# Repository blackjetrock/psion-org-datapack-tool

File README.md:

# psion-org-datapack-tool
Datapack tool for Psion Organisers

Status
======

** This is a work in progress and probably always will be **

The code builds and can read datapack data. It can also write datapack data. issues:
the OLED and buttons work and there are read and write and info options that work on the OLED.
A lot of funtionality is over USB serial.

0. There are errors on the fab1 PCB. these are listed in the errata. hand mods are needed to get the PCB to work.
1. Flash packs can't be written.
2. Read pak to file doesn't seem to give a valid opk file, not sure why
3. Detection of all the diffferent pack addressing schemes and sizes isn't there, really.
4. Could do with a detection routine.
5. The code is untidy...
6. The OLED and serial functions aren't very coherent.

Building
========

The firmware directory has the files required for building the code but
they are configured for my file system structure.
They will have to be altered to match the location of your SDK, where the FAT
FS library used will have to be located.

Set the PICO_SDK_DIR environment variable to point to the Pico SDK directory: 

export PICO_SDK_DIR="[where the Pico SDK is]"

create a 'build' directory in the 'firmware' directory and run:
cmake ..

then fix errors (should only be directories, probably the location of the FAT FS library in CMakeLists.txt)

Then :

make

Then program with either a picoprobe or as a UF2 file.

Picoprobe Programming
---------------------

There is a script in the firmware directory 

flash_code.sh

that will use openocd and a picprobe toprogram the code onto a Pico. 
Run this script from the build directory

../flash_code.sh

Openocd needs to be set up as detailed in the Pico documentation.
Some directories may need to be altered to match your structure.

There is also a script

../set_debug_openocd.sh

(also run from the build directory) that will set up gdb for a session. Run this from the 
build directory as well. It is set up to use the TUI (Text User Interface) 
with the -tui command line option, but that can be removed for a standard
gdb CLI experience.

Running
=======

There is an interface on the OLED display that uses the buttons. 

Left button:      Up
Middle Button:    Down
Right Button:     Action/Execute

There is a menu system to access all the functions.

There is also an interface that runs over the USB serial connectin from the 
Pico on the PCB to a host PC. I use minicom on Linux but any terminal emulator should work, 
e.g. the one in the Arduino SDK.

SD Card
=======

The SD card holds .opk images in a directory called 'PAK' that is located in the
root directory of the SD card. The SD card is checked at power on and a message 
appears on the OLED display indicating whether the check was OK or not.

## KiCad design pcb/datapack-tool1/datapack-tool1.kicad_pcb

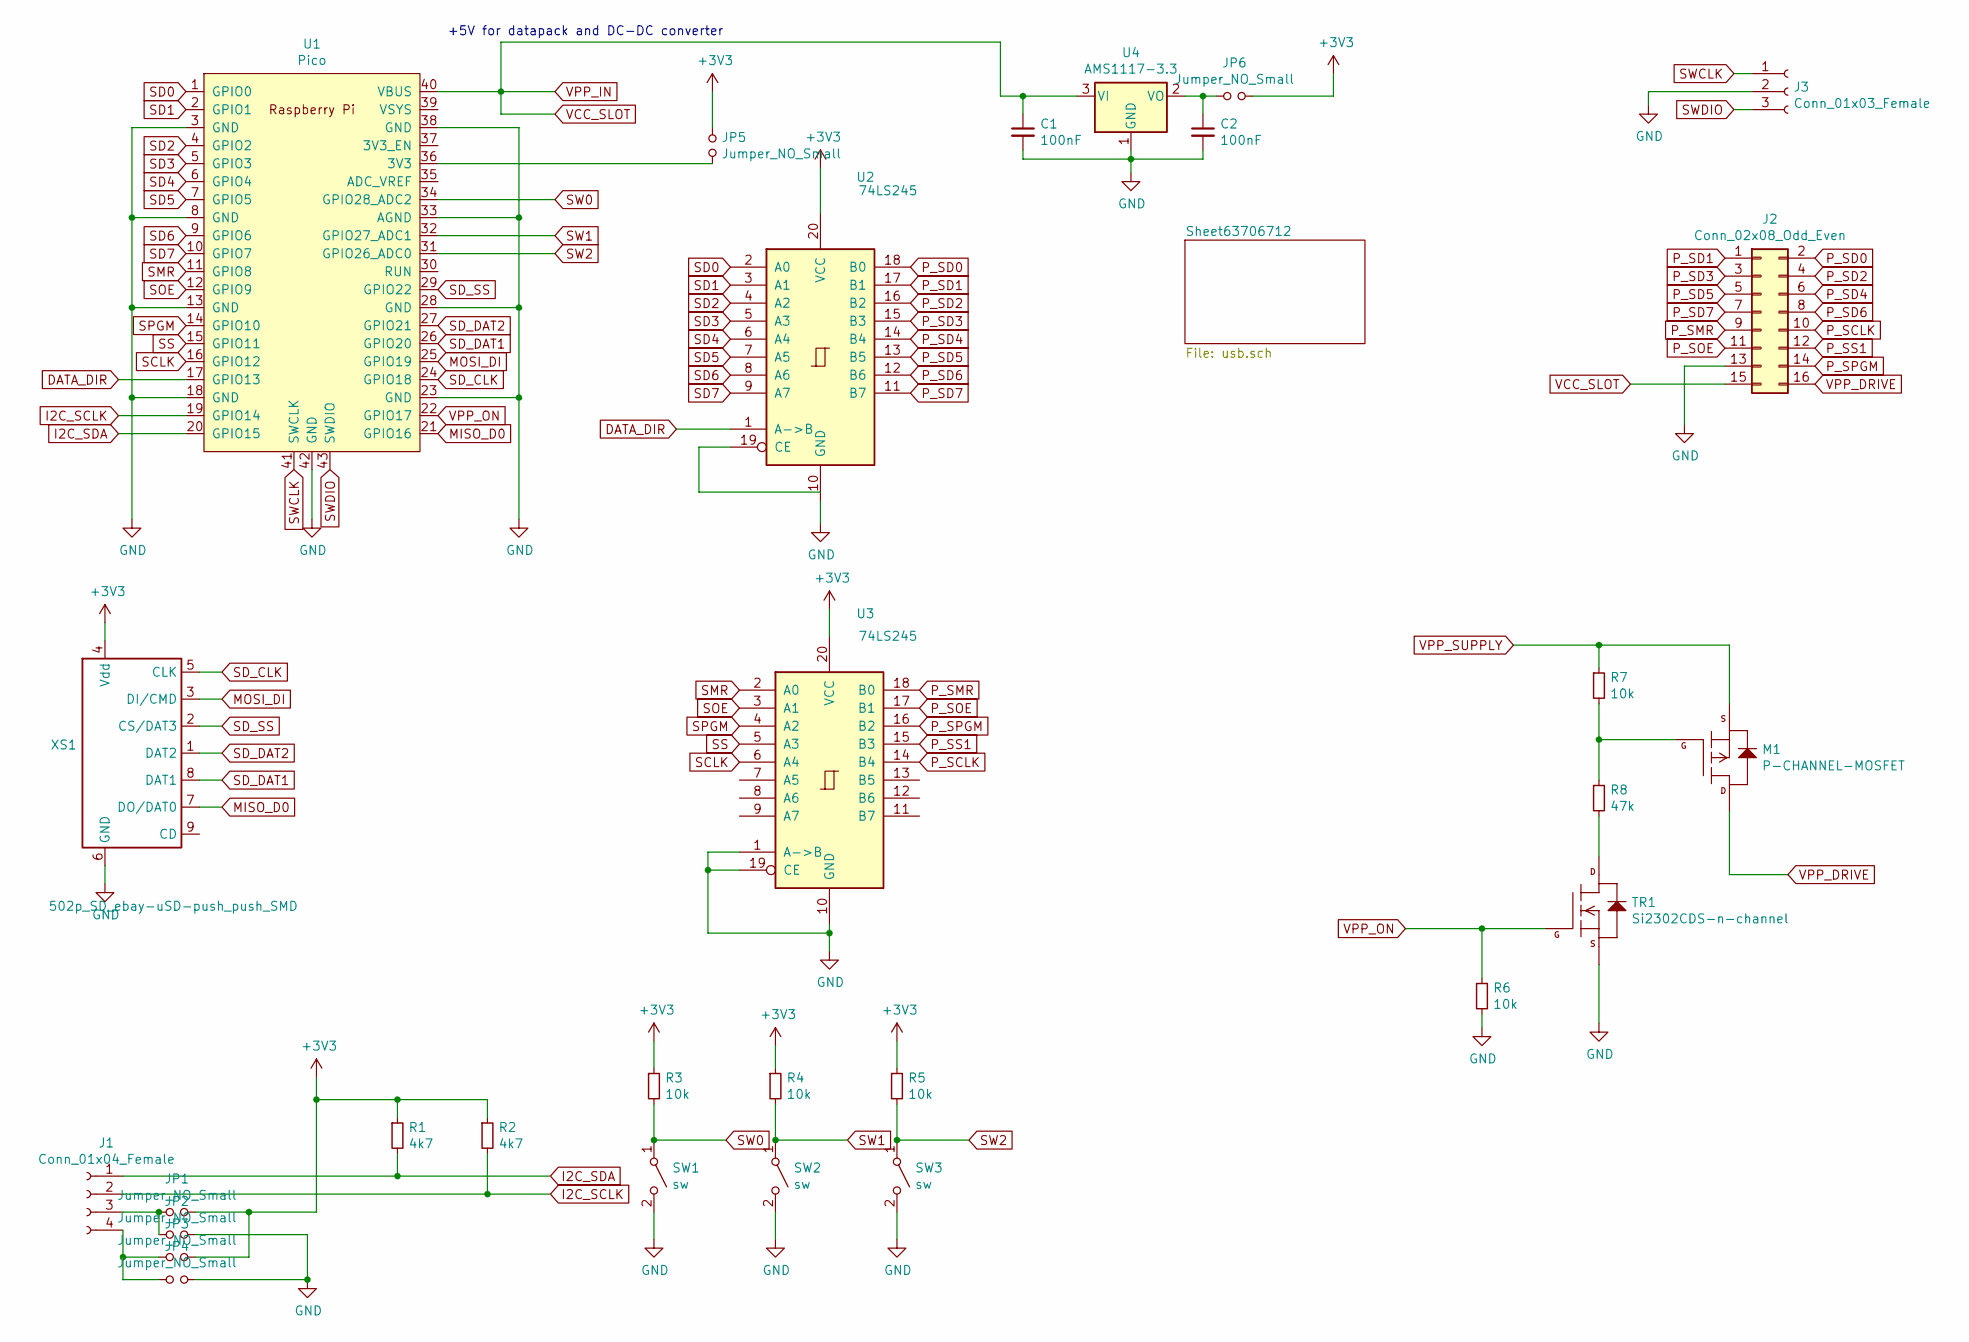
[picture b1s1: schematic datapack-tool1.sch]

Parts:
C1, C2: 100nF; C_0805_2012Metric
J1: Conn_01x04_Female; PinHeader_1x04_P2.54mm_Vertical
J2: Conn_02x08_Odd_Even; PinHeader_2x08_P2.54mm_Horizontal_psionSide
J3: Conn_01x03_Female; PinHeader_1x03_P2.54mm_Vertical
JP1, JP2, JP3, JP4, JP5, JP6: Jumper_NO_Small; SolderJumper-2_P1.3mm_Open_TrianglePad1.0x1.5mm
M1: P-CHANNEL-MOSFET; SOT-23
R1, R2: 4k7; C_0402_1005Metric
R3, R4, R5, R6, R7: 10k; R_0805_2012Metric
R8: 47k; R_0805_2012Metric
SW1, SW2, SW3: sw; SW_Push_1P1T_NO_Vertical_Wuerth_434133025816
TR1: Si2302CDS-n-channel; SOT-23
U1: Pico; RPi_Pico_SMD_TH
U2, U3: 74LS245; SOP-20_7.5x12.8mm_P1.27mm
U4: AMS1117-3.3; SOT-223-3_TabPin2
XS1: 502p_SD_ebay-uSD-push_push_SMD; Conn_uSDcard

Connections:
+3V3: JP1.2, JP3.2, JP5.1, JP6.2, R1.1, R2.1, R3.1, R4.1, R5.1, U2.20 (VCC), U3.20 (VCC), XS1.4 (Vdd)
DATA_DIR: U1.17 (GPIO13), U2.1 (A->B)
GND: C1.2, C2.2, J2.13, J3.2, JP2.2, JP4.2, R6.2, SW1.2 (B), SW2.2 (B), SW3.2 (B), TR1.2 (S), U1.3 (GND), U1.8 (GND), U1.13 (GND), U1.18 (GND), U1.23 (GND), U1.28 (GND), U1.33 (AGND), U1.38 (GND), U1.42 (GND), U2.10 (GND), U3.1 (A->B), U3.10 (GND), U3.19 (CE), U4.1 (GND), XS1.6 (GND); also elsewhere on the board
I2C_SCLK: J1.2, R2.2, U1.19 (GPIO14)
I2C_SDA: J1.1, R1.2, U1.20 (GPIO15)
MISO_D0: U1.21 (GPIO16), XS1.7 (DO/DAT0)
MOSI_DI: U1.25 (GPIO19), XS1.3 (DI/CMD)
unnamed: C2.1, JP6.1, U4.2 (VO)
unnamed: J1.3, JP1.1, JP2.1
unnamed: J1.4, JP3.1, JP4.1
unnamed: JP5.2, U1.36 (3V3)
unnamed: M1.1 (G), R7.2, R8.1
unnamed: R8.2, TR1.3 (D)
P_SCLK: J2.10, U3.14 (B4)
P_SD0: J2.2, U2.18 (B0)
P_SD1: J2.1, U2.17 (B1)
P_SD2: J2.4, U2.16 (B2)
P_SD3: J2.3, U2.15 (B3)
P_SD4: J2.6, U2.14 (B4)
P_SD5: J2.5, U2.13 (B5)
P_SD6: J2.8, U2.12 (B6)
P_SD7: J2.7, U2.11 (B7)
P_SMR: J2.9, U3.18 (B0)
P_SOE: J2.11, U3.17 (B1)
P_SPGM: J2.14, U3.16 (B2)
P_SS1: J2.12, U3.15 (B3)
SCLK: U1.16 (GPIO12), U3.6 (A4)
SD0: U1.1 (GPIO0), U2.2 (A0)
SD1: U1.2 (GPIO1), U2.3 (A1)
SD2: U1.4 (GPIO2), U2.4 (A2)
SD3: U1.5 (GPIO3), U2.5 (A3)
SD4: U1.6 (GPIO4), U2.6 (A4)
SD5: U1.7 (GPIO5), U2.7 (A5)
SD6: U1.9 (GPIO6), U2.8 (A6)
SD7: U1.10 (GPIO7), U2.9 (A7)
SD_CLK: U1.24 (GPIO18), XS1.5 (CLK)
SD_DAT1: U1.26 (GPIO20), XS1.8 (DAT1)
SD_DAT2: U1.27 (GPIO21), XS1.1 (DAT2)
SD_SS: U1.29 (GPIO22), XS1.2 (CS/DAT3)
SMR: U1.11 (GPIO8), U3.2 (A0)
SOE: U1.12 (GPIO9), U3.3 (A1)
SPGM: U1.14 (GPIO10), U3.4 (A2)
SS: U1.15 (GPIO11), U3.5 (A3)
SW0: R3.2, SW1.1 (A), U1.34 (GPIO28_ADC2)
SW1: R4.2, SW2.1 (A), U1.32 (GPIO27_ADC1)
SW2: R5.2, SW3.1 (A), U1.31 (GPIO26_ADC0)
SWCLK: J3.1, U1.41 (SWCLK)
SWDIO: J3.3, U1.43 (SWDIO)
VCC_SLOT: C1.1, J2.15, U1.40 (VBUS), U4.3 (VI); also elsewhere on the board
VPP_DRIVE: J2.16, M1.3 (D)
VPP_ON: R6.1, TR1.1 (G), U1.22 (GPIO17)
VPP_SUPPLY: M1.2 (S), R7.1; also elsewhere on the board

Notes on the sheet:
+5V for datapack and DC-DC converter

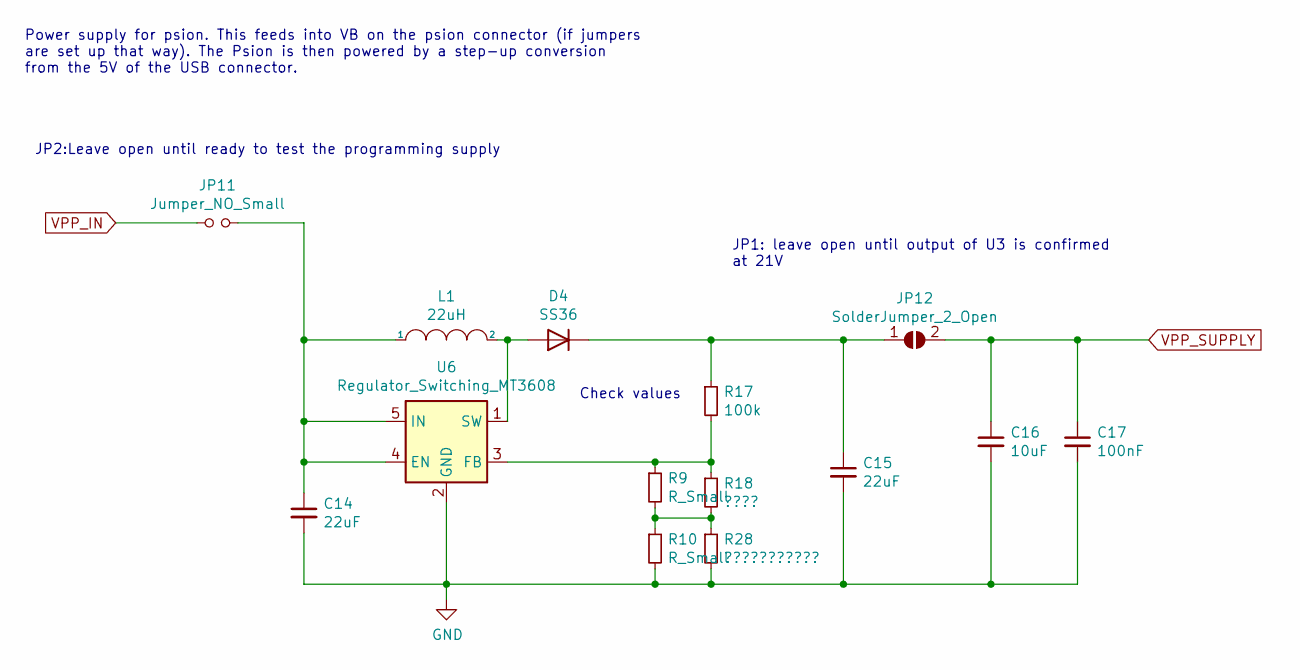
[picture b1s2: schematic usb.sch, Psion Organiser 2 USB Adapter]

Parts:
C14, C15: 22uF; C_1210_3225Metric_Pad1.33x2.70mm_HandSolder
C16: 10uF; C_1210_3225Metric_Pad1.33x2.70mm_HandSolder
C17: 100nF; C_0805_2012Metric
D4: SS36; D_SOD-123
JP11: Jumper_NO_Small; SolderJumper-2_P1.3mm_Open_Pad0.8x0.8mm
JP12: SolderJumper_2_Open; SolderJumper-2_P1.3mm_Open_Pad0.8x0.8mm
L1: 22uH; L_Coilcraft_LPS5030
R9, R10: R_Small; R_0805_2012Metric
R17: 100k; R_0805_2012Metric
R18: ????; R_0805_2012Metric
R28: ???????????; R_0805_2012Metric
U6: Regulator_Switching_MT3608; SOT-23-6

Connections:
GND: C14.2, C15.2, C16.2, C17.2, R10.2, R28.2, U6.2 (GND); also elsewhere on the board
unnamed: C14.1, JP11.2, L1.1, U6.4 (EN), U6.5 (IN)
unnamed: C15.1, D4.1 (K), JP12.1 (A), R17.1
unnamed: D4.2 (A), L1.2, U6.1 (SW)
unnamed: R9.2, R10.1, R18.2, R28.1
unnamed: R9.1, R17.2, R18.1, U6.3 (FB)
VCC_SLOT: JP11.1; also elsewhere on the board
VPP_SUPPLY: C16.1, C17.1, JP12.2 (B); also elsewhere on the board

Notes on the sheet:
Check values
JP1: leave open until output of U3 is confirmed at 21V
JP2:Leave open until ready to test the programming supply
Power supply for psion. This feeds into VB on the psion connector (if jumpers are set up that way). The Psion is then powered by a step-up conversion from the 5V of the USB connector.

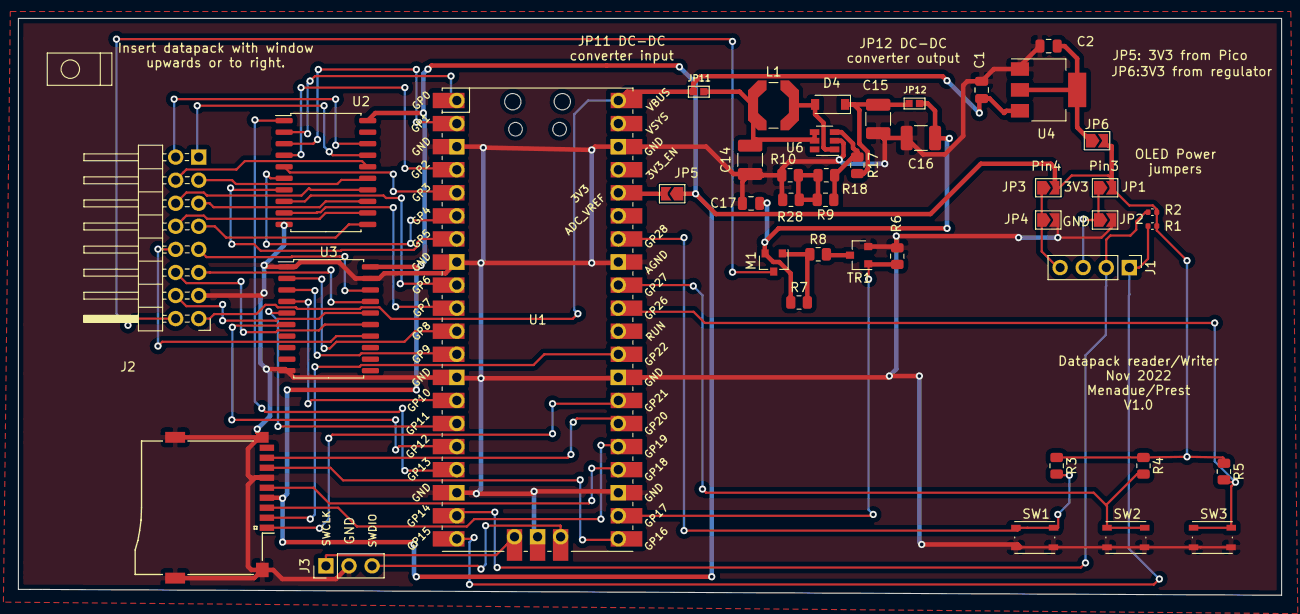
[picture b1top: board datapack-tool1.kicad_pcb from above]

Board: 2 copper layers, 139.1 x 63.5 mm, 43 parts (0 on the bottom side), 57 nets.

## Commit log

2022-12-24 Datapack can be read, code hacked about to find problem
2022-12-24 Tidy up. Managed to write a test record to a data pack using 18V as VPP
2023-01-26 Fixed reading a pack image
2023-01-29 Updated programming pulse times. Old ones worked, new ones work
2023-02-01 Changed delays to proper us, conditionally. Tidied warnings and fixed problem with USB serial locking up for some reason
